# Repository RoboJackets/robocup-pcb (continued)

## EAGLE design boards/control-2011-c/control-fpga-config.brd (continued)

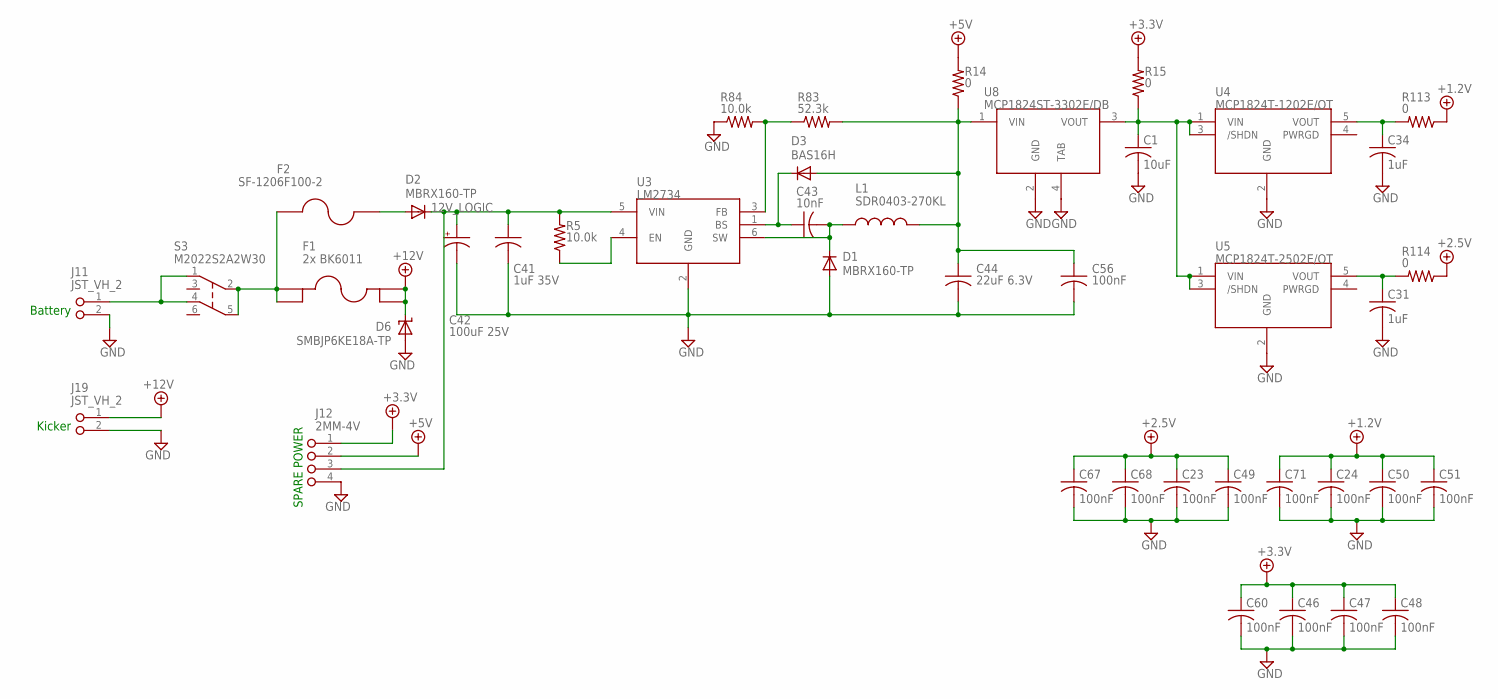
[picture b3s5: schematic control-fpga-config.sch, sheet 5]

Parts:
C1: 10uF; C0805
C23, C24, C46, C47, C48, C49, C50, C51, C56, C60, C67, C68, C71: 100nF; C0603
C31, C34: 1uF; C0603
C41: 1uF 35V; C0805
C42: 100uF 25V; PANASONIC_E
C43: 10nF; C0603
C44: 22uF 6.3V; C1206
D1, D2: MBRX160-TP; SOD123
D3: BAS16H; SOD323-W
D6: SMBJP6KE18A-TP; SMBJ
F1: 2x BK6011; FUSE_MINI_ATC
F2: SF-1206F100-2; F1206
J11, J19: JST_VH_2; JST_VH_2_RA
J12: 2MM-4V; 2MM-4-V
L1: SDR0403-270KL; SDR0403
R5, R84: 10.0k; R0603
R14, R15, R113, R114: 0; R0603
R83: 52.3k; R0603
S3: M2022S2A2W30; M202X-30
U3: LM2734; SOT23-6L
U4: MCP1824T-1202E/OT; SOT23-5
U5: MCP1824T-2502E/OT; SOT23-5
U8: MCP1824ST-3302E/DB; SOT223

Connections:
12V_LOGIC: C41.1, C42.+, D2.C, J12.3, R5.2, U3.5 (VIN)
+1.2V: C24.1, C50.1, C51.1, C71.1, R113.1; also elsewhere on the board
+2.5V: C23.1, C49.1, C67.1, C68.1, R114.1; also elsewhere on the board
+3.3V: C46.1, C47.1, C48.1, C60.1, J12.1, R15.2; also elsewhere on the board
+5V: J12.2, R14.2; also elsewhere on the board
+12V: D6.C, F1.3, F1.4, J19.1; also elsewhere on the board
GND: C1.2, C23.2, C24.2, C31.2, C34.2, C41.2, C42.-, C44.2, C46.2, C47.2, C48.2, C49.2, C50.2, C51.2, C56.2, C60.2, C67.2, C68.2, C71.2, D1.A, D6.A, J11.2, J12.4, J19.2, R84.1, U3.2 (GND), U4.2 (GND), U5.2 (GND), U8.2 (GND), U8.4 (TAB); also elsewhere on the board
unnamed: C44.1, C56.1, D3.A, L1.2, R14.1, R83.2, U8.1 (VIN)
unnamed: C1.1, R15.1, U4.1 (VIN), U4.3 (/SHDN), U5.1 (VIN), U5.3 (/SHDN), U8.3 (VOUT)
unnamed: C43.2, D1.C, L1.1, U3.6 (SW)
unnamed: C34.1, R113.2, U4.5 (VOUT)
unnamed: C31.1, R114.2, U5.5 (VOUT)
unnamed: J11.1, S3.1 (NC1), S3.4 (NC2)
unnamed: R5.1, U3.4 (EN)
unnamed: C43.1, D3.C, U3.1 (BS)
unnamed: F1.1, F1.2, F2.1, S3.2 (C1), S3.5 (C2)
unnamed: R83.1, R84.2, U3.3 (FB)
unnamed: D2.A, F2.2

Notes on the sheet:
Kicker
Battery
SPARE POWER

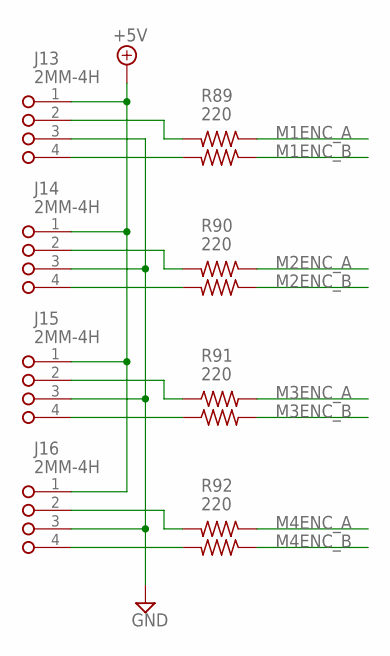
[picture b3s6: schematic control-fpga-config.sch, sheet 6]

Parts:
J13, J14, J15, J16: 2MM-4H; 2MM-4-H
R89, R90, R91, R92: 220; RA_2_0606

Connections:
+5V: J13.1, J14.1, J15.1, J16.1; also elsewhere on the board
GND: J13.3, J14.3, J15.3, J16.3; also elsewhere on the board
M1ENC_A: R89.1; also elsewhere on the board
M1ENC_B: R89.3; also elsewhere on the board
M2ENC_A: R90.1; also elsewhere on the board
M2ENC_B: R90.3; also elsewhere on the board
M3ENC_A: R91.2; also elsewhere on the board
M3ENC_B: R91.4; also elsewhere on the board
M4ENC_A: R92.1; also elsewhere on the board
M4ENC_B: R92.3; also elsewhere on the board
unnamed: J13.4, R89.4
unnamed: J13.2, R89.2
unnamed: J16.4, R92.4
unnamed: J16.2, R92.2
unnamed: J15.4, R91.3
unnamed: J15.2, R91.1
unnamed: J14.4, R90.4
unnamed: J14.2, R90.2

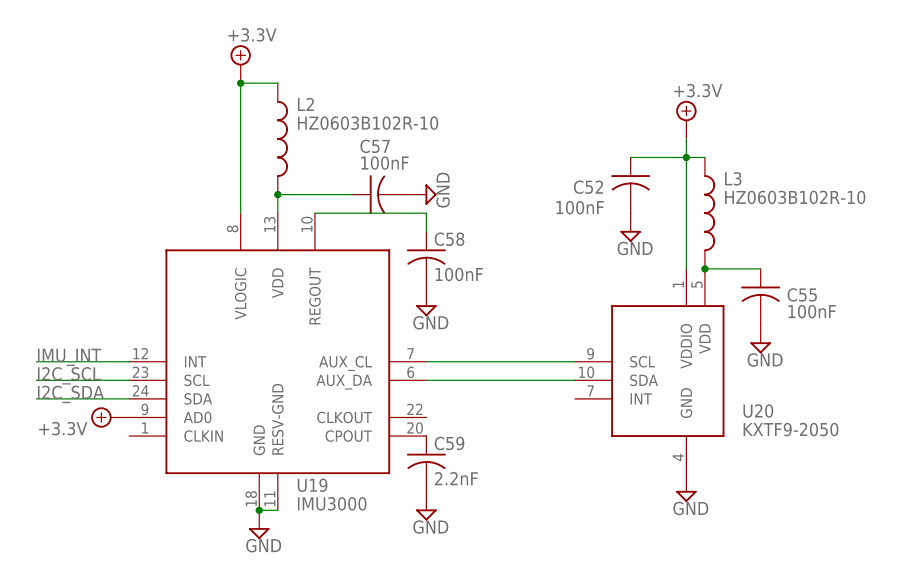
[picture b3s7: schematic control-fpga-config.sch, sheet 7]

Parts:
C52, C55, C57, C58: 100nF; C0603
C59: 2.2nF; C0603
L2, L3: HZ0603B102R-10; C0603
U19: IMU3000
U20: KXTF9-2050; KXTF9

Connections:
+3.3V: C52.1, L2.1, L3.1, U19.8 (VLOGIC), U19.9 (AD0), U20.1 (VDDIO); also elsewhere on the board
GND: C52.2, C55.2, C57.2, C58.2, C59.2, U19.11 (RESV-GND), U19.18 (GND), U20.4 (GND); also elsewhere on the board
I2C_SCL: U19.23 (SCL); also elsewhere on the board
I2C_SDA: U19.24 (SDA); also elsewhere on the board
IMU_INT: U19.12 (INT); also elsewhere on the board
unnamed: C55.1, L3.2, U20.5 (VDD)
unnamed: U19.7 (AUX_CL), U20.9 (SCL)
unnamed: U19.6 (AUX_DA), U20.10 (SDA)
unnamed: C57.1, L2.2, U19.13 (VDD)
unnamed: C58.1, U19.10 (REGOUT)
unnamed: C59.1, U19.20 (CPOUT)

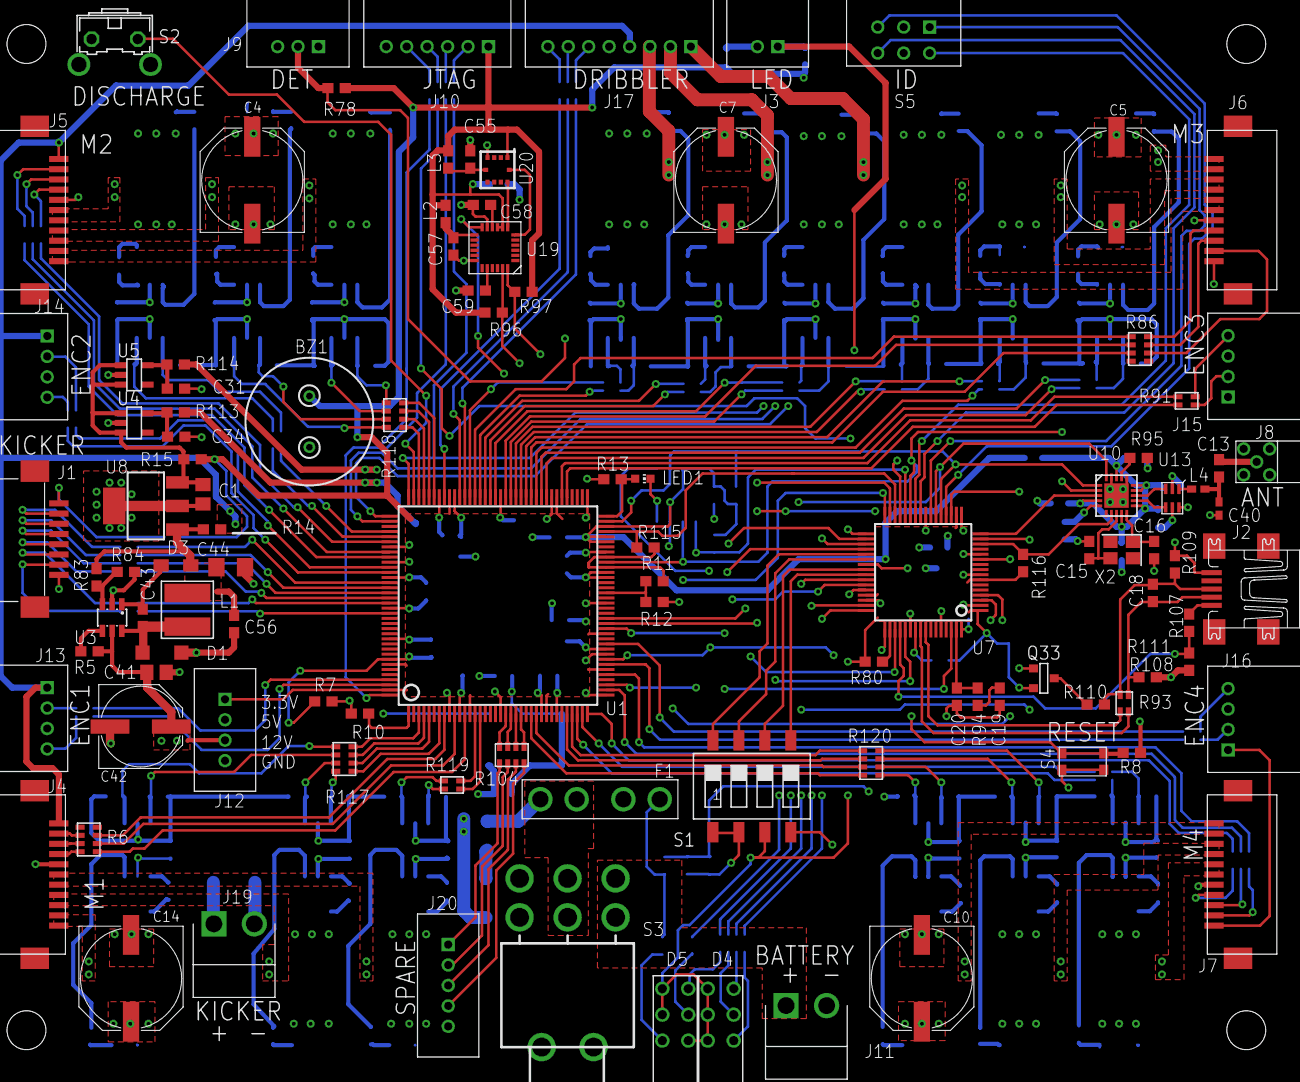
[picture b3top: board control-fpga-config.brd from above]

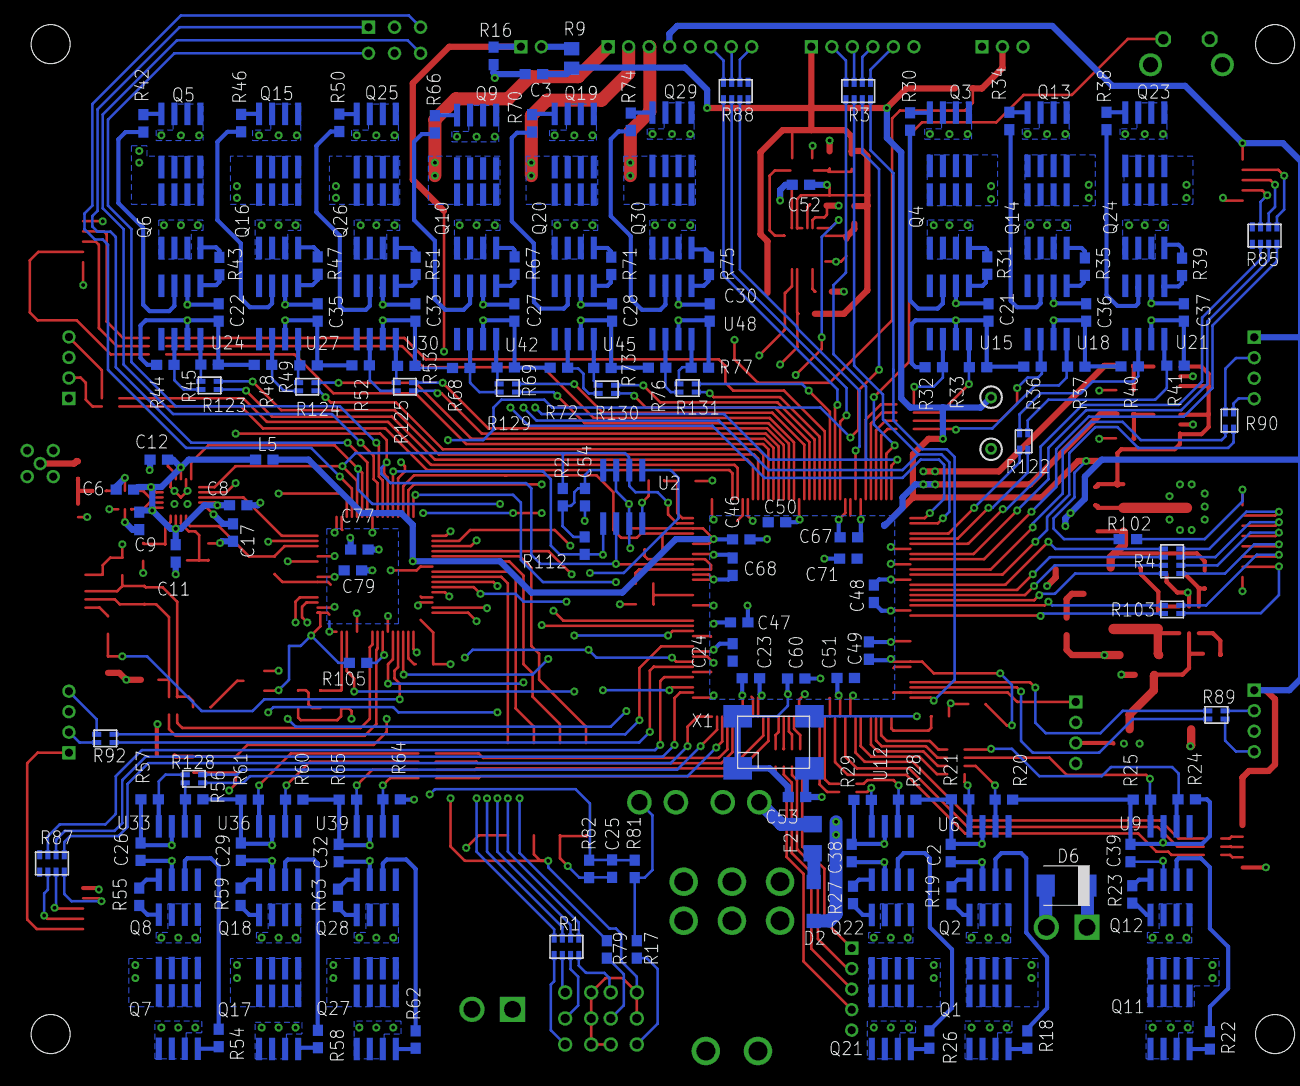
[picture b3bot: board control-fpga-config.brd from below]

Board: 4 copper layers, 285 parts (179 on the bottom side), 301 nets.

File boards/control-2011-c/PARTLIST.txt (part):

Partlist

Exported from control-2011-c.brd at 10/16/2014 2:49:54 AM

EAGLE Version 6.5.0 Copyright (c) 1988-2013 CadSoft

Assembly variant: 

Part     Value              Package         Library          Position (inch)       Orientation

BZ1      PS12               PS12            tdk              (1.09 2.345)          R90
C1       10uF               C0805           rcl              (0.68 2.065)          R270
C2       100nF              C0603           rcl              (1.245 0.695)         MR90
C3       1uF                C0603           rcl              (2.845 3.685)         MR180
C4       470uF 25V          PANASONIC_G     rcl              (0.87 3.275)          R90
C5       470uF 25V          PANASONIC_G     rcl              (4.2 3.275)           R90
C6       100nF              C0603           rcl              (4.415 2.09)          MR180
C7       470uF 25V          PANASONIC_G     rcl              (2.695 3.275)         R90
C8       10nF               C0603           rcl              (3.98 2.03)           MR0
C9       2.2nF              C0603           rcl              (4.36 1.97)           MR270
C10      470uF 25V          PANASONIC_G     rcl              (3.45 0.2)            R270
C11      10nF               C0603           rcl              (4.22 1.845)          MR270
C12      220nF              C0603           rcl              (4.285 2.205)         MR180
C13      100pF              C0603           rcl              (4.595 2.165)         R90
C14      470uF 25V          PANASONIC_G     rcl              (0.403 0.2)           R270
C15      27pF               C0603           rcl              (4.095 1.85)          R90
C16      27pF               C0603           rcl              (4.345 1.85)          R270
C17      100nF              C0603           rcl              (4 1.925)             MR270
C18      33pF               C0603           rcl              (4.34 1.685)          R270
C19      10nF               C0603           rcl              (3.75 1.285)          R270
C20      1nF                C0603           rcl              (3.585 1.285)         R270
C21      100nF              C0603           rcl              (1.1 2.77)            MR270
C22      100nF              C0603           rcl              (4.055 2.77)          MR270
C23      100nF              C0603           rcl              (2.012 1.366)         MR0
C24      100nF              C0603           rcl              (2.082 1.465)         MR90
C25      100nF              C0603           rcl              (2.545 0.635)         MR270
C26      100nF              C0603           rcl              (4.355 0.7)           MR90
C27      100nF              C0603           rcl              (2.92 2.77)           MR270
C28      100nF              C0603           rcl              (2.545 2.77)          MR270
C29      100nF              C0603           rcl              (3.97 0.7)            MR90
C30      100nF              C0603           rcl              (2.17 2.77)           MR270
C31      1uF                C0603           rcl              (0.576 2.472)         R0
C32      100nF              C0603           rcl              (3.595 0.695)         MR90
C33      100nF              C0603           rcl              (3.3 2.77)            MR270
C34      1uF                C0603           rcl              (0.577 2.287)         R0
C35      100nF              C0603           rcl              (3.675 2.77)          MR270
C36      100nF              C0603           rcl              (0.725 2.77)          MR270
C37      100nF              C0603           rcl              (0.35 2.77)           MR270
C38      100nF              C0603           rcl              (1.625 0.695)         MR90
C39      100nF              C0603           rcl              (0.555 0.695)         MR90
C40      500R07S1R8BV4T     C0402           rcl              (4.595 2.01)          R270
C41      1uF 35V            C0805           rcl              (0.501 1.379)         R0
C42      100uF 25V          PANASONIC_E     rcl              (0.44 1.17)           R0
C43      10nF               C0603           rcl              (0.448 1.589)         R270
C44      22uF 6.3V          C1206           rcl              (0.787 1.784)         R0
C46      100nF              C0603           rcl              (2.049 1.899)         MR0
C47      100nF              C0603           rcl              (2.057 1.58)          MR0
C48      100nF              C0603           rcl              (1.54 1.69)           MR270
C49      100nF              C0603           rcl              (1.559 1.472)         MR90
C50      100nF              C0603           rcl              (1.912 1.965)         MR0
C51      100nF              C0603           rcl              (1.648 1.367)         MR180
C52      100nF              C0603           rcl              (1.82 3.26)           MR180
C53      100nF              C0603           rcl              (1.835 0.91)          MR0
C54      100nF              C0603           rcl              (2.649 2.061)         MR270
C55      100nF              C0603           rcl              (1.71 3.355)          R90
C56      100nF              C0603           rcl              (0.8 1.565)           R270
C57      100nF              C0603           rcl              (1.645 3.02)          R270
C58      100nF              C0603           rcl              (1.755 3.18)          R180
C59      2.2nF              C0603           rcl              (1.735 2.85)          R180
C60      100nF              C0603           rcl              (1.838 1.365)         MR0
C67      100nF              C0603           rcl              (1.636 1.907)         MR180
C68      100nF              C0603           rcl              (2.082 1.794)         MR270
C71      100nF              C0603           rcl              (1.638 1.825)         MR180
C77      100nF              C0603           rcl              (3.515 1.86)          MR0
C79      100nF              C0603           rcl              (3.54 1.78)           MR0
D1       MBRX160-TP         SOD123          diode            (0.522 1.455)         R0
D2       MBRX160-TP         SOD123          diode            (1.771 0.509)         MR90
D3       BAS16H             SOD323-W        diode            (0.576 1.791)         R0
D4       564-0100-132F      DIALIGHT-564    led-array        (2.625 -0.04)         R0
D5       564-0100-132F      DIALIGHT-564    led-array        (2.45 -0.04)          R0
D6       SMBJP6KE18A-TP     SMBJ            power            (0.8 0.57)            MR180
F1       2x BK6011          FUSE_MINI_ATC   power            (2.21 0.89)           R0
F2       SF-1206F100-2      F1206           power            (1.775 0.75)          MR270
J1       0528520870         0528520870      con-robocup      (0.125 2.03)          R270
J2       MINI-USB           UX60A-MB-5ST    con-robocup      (4.655 1.7)           R180
J3       2MM-2H             2MM-2-H         2mm              (2.895 3.79)          R0
J4       Molex 0522711179   FH_11_HOR       hirose           (0.15 0.6)            R90
J5       Molex 0522711179   FH_11_HOR       hirose           (0.15 3.16)           R90
J6       Molex 0522711179   FH_11_HOR       hirose           (4.55 3.16)           R270
J7       Molex 0522711179   FH_11_HOR       hirose           (4.55 0.6)            R270
J8       MMCX_RA            MMCX_RA         radio            (4.74 2.19)           R0
J9       2MM-3H             2MM-3-H         2mm              (1.125 3.79)          R0
J10      2MM-6H             2MM-6-H         2mm              (1.78 3.79)           R0
J11      JST_VH_2           JST_VH_2_RA     jst_vh           (3.005 0.095)         R0
J12      2MM-4V             2MM-4-V         2mm              (0.765 1.275)         R90
J13      2MM-4H             2MM-4-H         2mm              (0.08 1.32)           R90
J14      2MM-4H             2MM-4-H         2mm              (0.08 2.675)          R90
J15      2MM-4H             2MM-4-H         2mm              (4.63 2.44)           R270
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
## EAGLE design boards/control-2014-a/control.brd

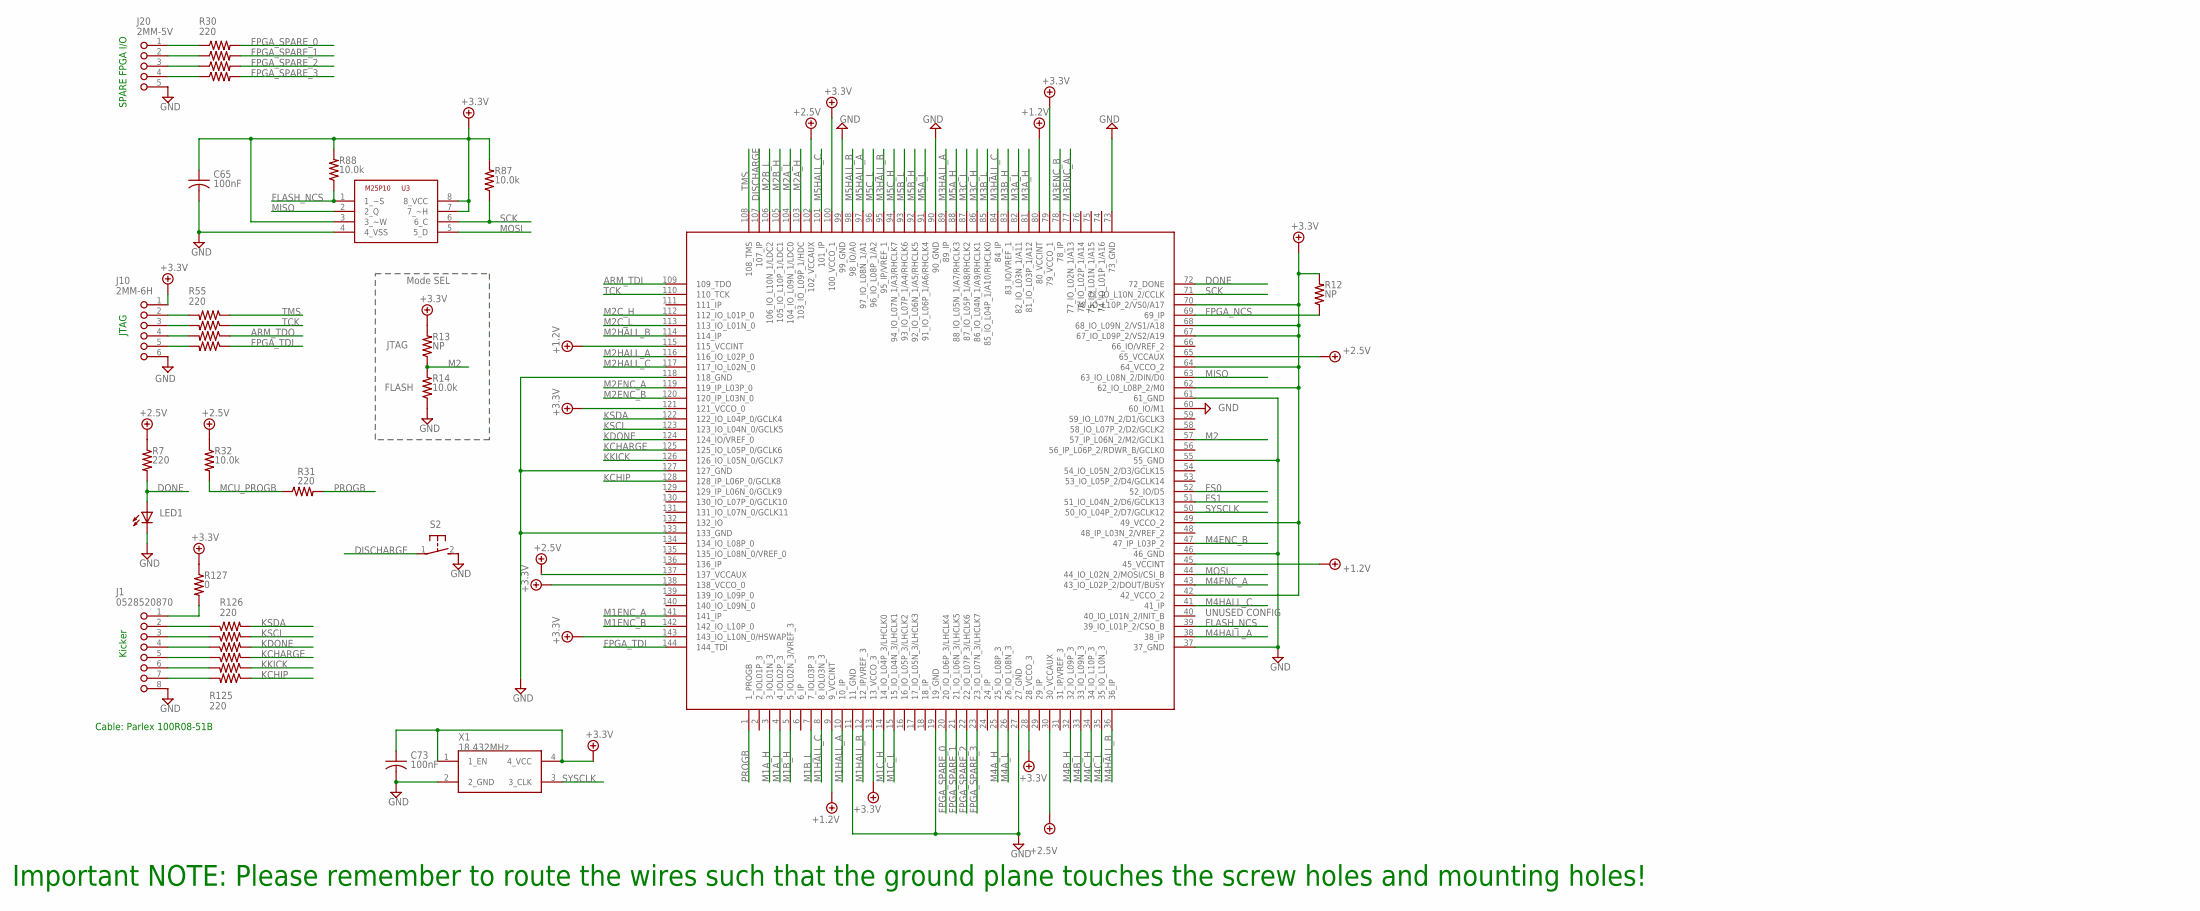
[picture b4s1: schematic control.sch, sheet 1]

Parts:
C65, C73: 100nF; C0603
J1: 0528520870
J10: 2MM-6H; 2MM-6-H
J20: 2MM-5V; 2MM-5-V
LED1: LEDCHIP-LED0603; CHIP-LED0603
R7, R31: 220; R0603
R12, R13: NP; R0603
R14, R32, R87, R88: 10.0k; R0603
R30, R55, R126: 220; RA_4_1206
R125: 220; RA_2_0606
R127: 0; R0603
S2: 31-XX; B3F-31XX
U1: XC3S100E; TQFP144
U3: M25P10; SO08
X1: 18.432MHz; XTAL_LCC

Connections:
+1.2V: U1.9 (9_VCCINT), U1.45 (45_VCCINT), U1.80 (80_VCCINT), U1.115 (115_VCCINT); also elsewhere on the board
+2.5V: R7.1, R32.1, U1.30 (30_VCCAUX), U1.65 (65_VCCAUX), U1.102 (102_VCCAUX), U1.137 (137_VCCAUX); also elsewhere on the board
+3.3V: C65.1, C73.1, J10.1, R12.2, R13.2, R87.2, R88.2, R127.1, U1.13 (13_VCCO_3), U1.28 (28_VCCO_3), U1.42 (42_VCCO_2), U1.49 (49_VCCO_2), U1.62 (62_IO_L08P_2/M0), U1.64 (64_VCCO_2), U1.67 (67_IO_L09P_2/VS2/A19), U1.68 (68_IO_L09N_2/VS1/A18), U1.70 (70_IO_L10P_2/VS0/A17), U1.79 (79_VCCO_1), U1.100 (100_VCCO_1), U1.121 (121_VCCO_0), U1.138 (138_VCCO_0), U1.143 (143_IO_L10N_0/HSWAP), U3.3 (3_~W), U3.7 (7_~H), U3.8 (8_VCC), X1.1 (1_EN), X1.4 (4_VCC); also elsewhere on the board
ARM_TDI: U1.109 (109_TDO); also elsewhere on the board
ARM_TDO: R55.5; also elsewhere on the board
DISCHARGE: S2.1, U1.107 (107_IP)
DONE: LED1.A, R7.2, U1.72 (72_DONE)
FLASH_NCS: R88.1, U1.39 (39_IO_L01P_2/CSO_B), U3.1 (1_~S); also elsewhere on the board
FPGA_NCS: R12.1, U1.69 (69_IP); also elsewhere on the board
FPGA_SPARE_0: R30.2, U1.20 (20_IO_L06P_3/LHCLK4)
FPGA_SPARE_1: R30.4, U1.21 (21_IO_L06N_3/LHCLK5)
FPGA_SPARE_2: R30.6, U1.22 (22_IO_L07P_3/LHCLK6)
FPGA_SPARE_3: R30.8, U1.23 (23_IO_L07N_3/LHCLK7)
FPGA_TDI: R55.7, U1.144 (144_TDI)
FS0: U1.52 (52_IO/D5); also elsewhere on the board
FS1: U1.51 (51_IO_L04N_2/D6/GCLK13); also elsewhere on the board
GND: C65.2, C73.2, J1.8, J10.6, J20.5, LED1.C, R14.1, S2.2 (S), U1.11 (11_GND), U1.19 (19_GND), U1.27 (27_GND), U1.37 (37_GND), U1.46 (46_GND), U1.55 (55_GND), U1.60 (60_IO/M1), U1.61 (61_GND), U1.73 (73_GND), U1.90 (90_GND), U1.99 (99_GND), U1.118 (118_GND), U1.127 (127_GND), U1.133 (133_GND), U3.4 (4_VSS), X1.2 (2_GND); also elsewhere on the board
KCHARGE: R126.2, U1.125 (125_IO_L05P_0/GCLK6)
KCHIP: R125.3, U1.128 (128_IP_L06P_0/GCLK8)
KDONE: R126.4, U1.124 (124_IO/VREF_0)
KKICK: R125.1, U1.126 (126_IO_L05N_0/GCLK7)
KSCL: R126.6, U1.123 (123_IO_L04N_0/GCLK5)
KSDA: R126.8, U1.122 (122_IO_L04P_0/GCLK4)
M1A_H: U1.3 (3_IOL01N_3); also elsewhere on the board
M1A_L: U1.4 (4_IOL02P_3); also elsewhere on the board
M1B_H: U1.5 (5_IOL02N_3/VREF_3); also elsewhere on the board
M1B_L: U1.7 (7_IOL03P_3); also elsewhere on the board
M1C_H: U1.14 (14_IO_L04P_3/LHCLK0); also elsewhere on the board
M1C_L: U1.15 (15_IO_L04N_3/LHCLK1); also elsewhere on the board
M1ENC_A: U1.141 (141_IP); also elsewhere on the board
M1ENC_B: U1.142 (142_IO_L10P_0); also elsewhere on the board
M1HALL_A: U1.10 (10_IP); also elsewhere on the board
M1HALL_B: U1.12 (12_IP/VREF_3); also elsewhere on the board
M1HALL_C: U1.8 (8_IOL03N_3); also elsewhere on the board
M2: R13.1, R14.2, U1.57 (57_IP_L06N_2/M2/GCLK1)
M2A_H: U1.103 (103_IO_L09P_1/HDC); also elsewhere on the board
M2A_L: U1.104 (104_IO_L09N_1/LDC0); also elsewhere on the board
M2B_H: U1.105 (105_IO_L10P_1/LDC1); also elsewhere on the board
M2B_L: U1.106 (106_IO_L10N_1/LDC2); also elsewhere on the board
M2C_H: U1.112 (112_IO_L01P_0); also elsewhere on the board
M2C_L: U1.113 (113_IO_L01N_0); also elsewhere on the board
M2ENC_A: U1.119 (119_IP_L03P_0); also elsewhere on the board
M2ENC_B: U1.120 (120_IP_L03N_0); also elsewhere on the board
M2HALL_A: U1.116 (116_IO_L02P_0); also elsewhere on the board
M2HALL_B: U1.114 (114_IP); also elsewhere on the board
M2HALL_C: U1.117 (117_IO_L02N_0); also elsewhere on the board
M3A_H: U1.81 (81_IO_L03P_1/A12); also elsewhere on the board
M3A_L: U1.82 (82_IO_L03N_1/A11); also elsewhere on the board
M3B_H: U1.83 (83_IO/VREF_1); also elsewhere on the board
M3B_L: U1.85 (85_IO_L04P_1/A10/RHCLK0); also elsewhere on the board
M3C_H: U1.86 (86_IO_L04N_1/A9/RHCLK1); also elsewhere on the board
M3C_L: U1.87 (87_IO_L05P_1/A8/RHCLK2); also elsewhere on the board
M3ENC_A: U1.77 (77_IO_L02N_1/A13); also elsewhere on the board
M3ENC_B: U1.78 (78_IP); also elsewhere on the board
M3HALL_A: U1.89 (89_IP); also elsewhere on the board
M3HALL_B: U1.95 (95_IP/VREF_1); also elsewhere on the board
M3HALL_C: U1.84 (84_IP); also elsewhere on the board
M4A_H: U1.25 (25_IO_L08P_3); also elsewhere on the board
M4A_L: U1.26 (26_IO_L08N_3); also elsewhere on the board
M4B_H: U1.32 (32_IO_L09P_3); also elsewhere on the board
M4B_L: U1.33 (33_IO_L09N_3); also elsewhere on the board
M4C_H: U1.34 (34_IO_L10P_3); also elsewhere on the board
M4C_L: U1.35 (35_IO_L10N_3); also elsewhere on the board
M4ENC_A: U1.43 (43_IO_L02P_2/DOUT/BUSY); also elsewhere on the board
M4ENC_B: U1.47 (47_IP_L03P_2); also elsewhere on the board
M4HALL_A: U1.38 (38_IP); also elsewhere on the board
M4HALL_B: U1.36 (36_IP); also elsewhere on the board
M4HALL_C: U1.41 (41_IP); also elsewhere on the board
M5A_H: U1.88 (88_IO_L05N_1/A7/RHCLK3); also elsewhere on the board
M5A_L: U1.91 (91_IO_L06P_1/A6/RHCLK4); also elsewhere on the board
M5B_H: U1.92 (92_IO_L06N_1/A5/RHCLK5); also elsewhere on the board
M5B_L: U1.93 (93_IO_L07P_1/A4/RHCLK6); also elsewhere on the board
M5C_H: U1.94 (94_IO_L07N_1/A3/RHCLK7); also elsewhere on the board
M5C_L: U1.96 (96_IO_L08P_1/A2); also elsewhere on the board
M5HALL_A: U1.97 (97_IO_L08N_1/A1); also elsewhere on the board
M5HALL_B: U1.98 (98_IO/A0); also elsewhere on the board
M5HALL_C: U1.101 (101_IP); also elsewhere on the board
MCU_PROGB: R31.1, R32.2; also elsewhere on the board
MISO: U1.63 (63_IO_L08N_2/DIN/D0), U3.2 (2_Q); also elsewhere on the board
MOSI: U1.44 (44_IO_L02N_2/MOSI/CSI_B), U3.5 (5_D); also elsewhere on the board
unnamed: J10.3, R55.4
unnamed: J10.5, R55.8
unnamed: J1.2, R126.7
unnamed: J1.3, R126.5
unnamed: J1.4, R126.3
unnamed: J1.5, R126.1
unnamed: J10.4, R55.6
unnamed: J10.2, R55.2
unnamed: J1.6, R125.2
unnamed: J1.7, R125.4
unnamed: J1.1, R127.2
unnamed: J20.3, R30.5
unnamed: J20.2, R30.3
unnamed: J20.1, R30.1
unnamed: J20.4, R30.7
PROGB: R31.2, U1.1 (1_PROGB)
SCK: R87.1, U1.71 (71_IO_L10N_2/CCLK), U3.6 (6_C); also elsewhere on the board
SYSCLK: U1.50 (50_IO_L04P_2/D7/GCLK12), X1.3 (3_CLK); also elsewhere on the board
TCK: R55.3, U1.110 (110_TCK); also elsewhere on the board
TMS: R55.1, U1.108 (108_TMS); also elsewhere on the board

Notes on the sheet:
JTAG
FLASH
Mode SEL
Kicker
UNUSED CONFIG
SPARE FPGA I/O
Cable: Parlex 100R08-51B
Important NOTE: Please remember to route the wires such that the ground plane touches the screw holes and mounting holes!

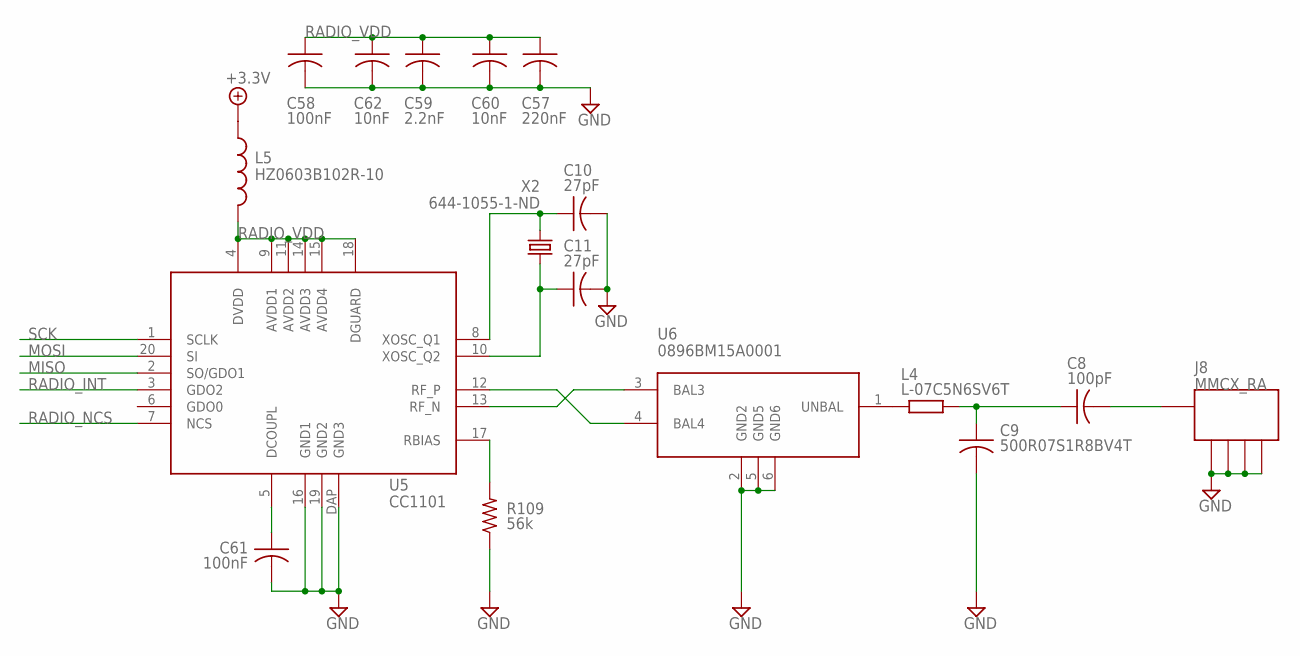
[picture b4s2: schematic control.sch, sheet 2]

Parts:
C8: 100pF; C0603
C9: 500R07S1R8BV4T; C0402
C10, C11: 27pF; C0603
C57: 220nF; C0603
C58, C61: 100nF; C0603
C59: 2.2nF; C0603
C60, C62: 10nF; C0603
J8: MMCX_RA
L4: L-07C5N6SV6T; R0402
L5: HZ0603B102R-10; C0603
R109: 56k; R0603
U5: CC1101; QLP20
U6: 0896BM15A0001
X2: 644-1055-1-ND; XTAL-3.2X2.5

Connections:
+3.3V: L5.1; also elsewhere on the board
GND: C9.2, C10.2, C11.2, C57.2, C58.2, C59.2, C60.2, C61.2, C62.2, J8.P$2, J8.P$3, J8.P$4, J8.P$5, R109.1, U5.16 (GND1), U5.19 (GND2), U5.DAP (GND3), U6.2 (GND2), U6.5 (GND5), U6.6 (GND6); also elsewhere on the board
MISO: U5.2 (SO/GDO1); also elsewhere on the board
MOSI: U5.20 (SI); also elsewhere on the board
unnamed: C61.1, U5.5 (DCOUPL)
unnamed: R109.2, U5.17 (RBIAS)
unnamed: C11.1, U5.10 (XOSC_Q2), X2.1
unnamed: C10.1, U5.8 (XOSC_Q1), X2.3 (2)
unnamed: L4.1, U6.1 (UNBAL)
unnamed: C8.1, C9.1, L4.2
unnamed: U5.12 (RF_P), U6.4 (BAL4)
unnamed: U5.13 (RF_N), U6.3 (BAL3)
unnamed: C8.2, J8.P$1
RADIO_INT: U5.3 (GDO2); also elsewhere on the board
RADIO_NCS: U5.7 (NCS); also elsewhere on the board
RADIO_VDD: C57.1, C58.1, C59.1, C60.1, C62.1, L5.2, U5.4 (DVDD), U5.9 (AVDD1), U5.11 (AVDD2), U5.14 (AVDD3), U5.15 (AVDD4), U5.18 (DGUARD)
SCK: U5.1 (SCLK); also elsewhere on the board

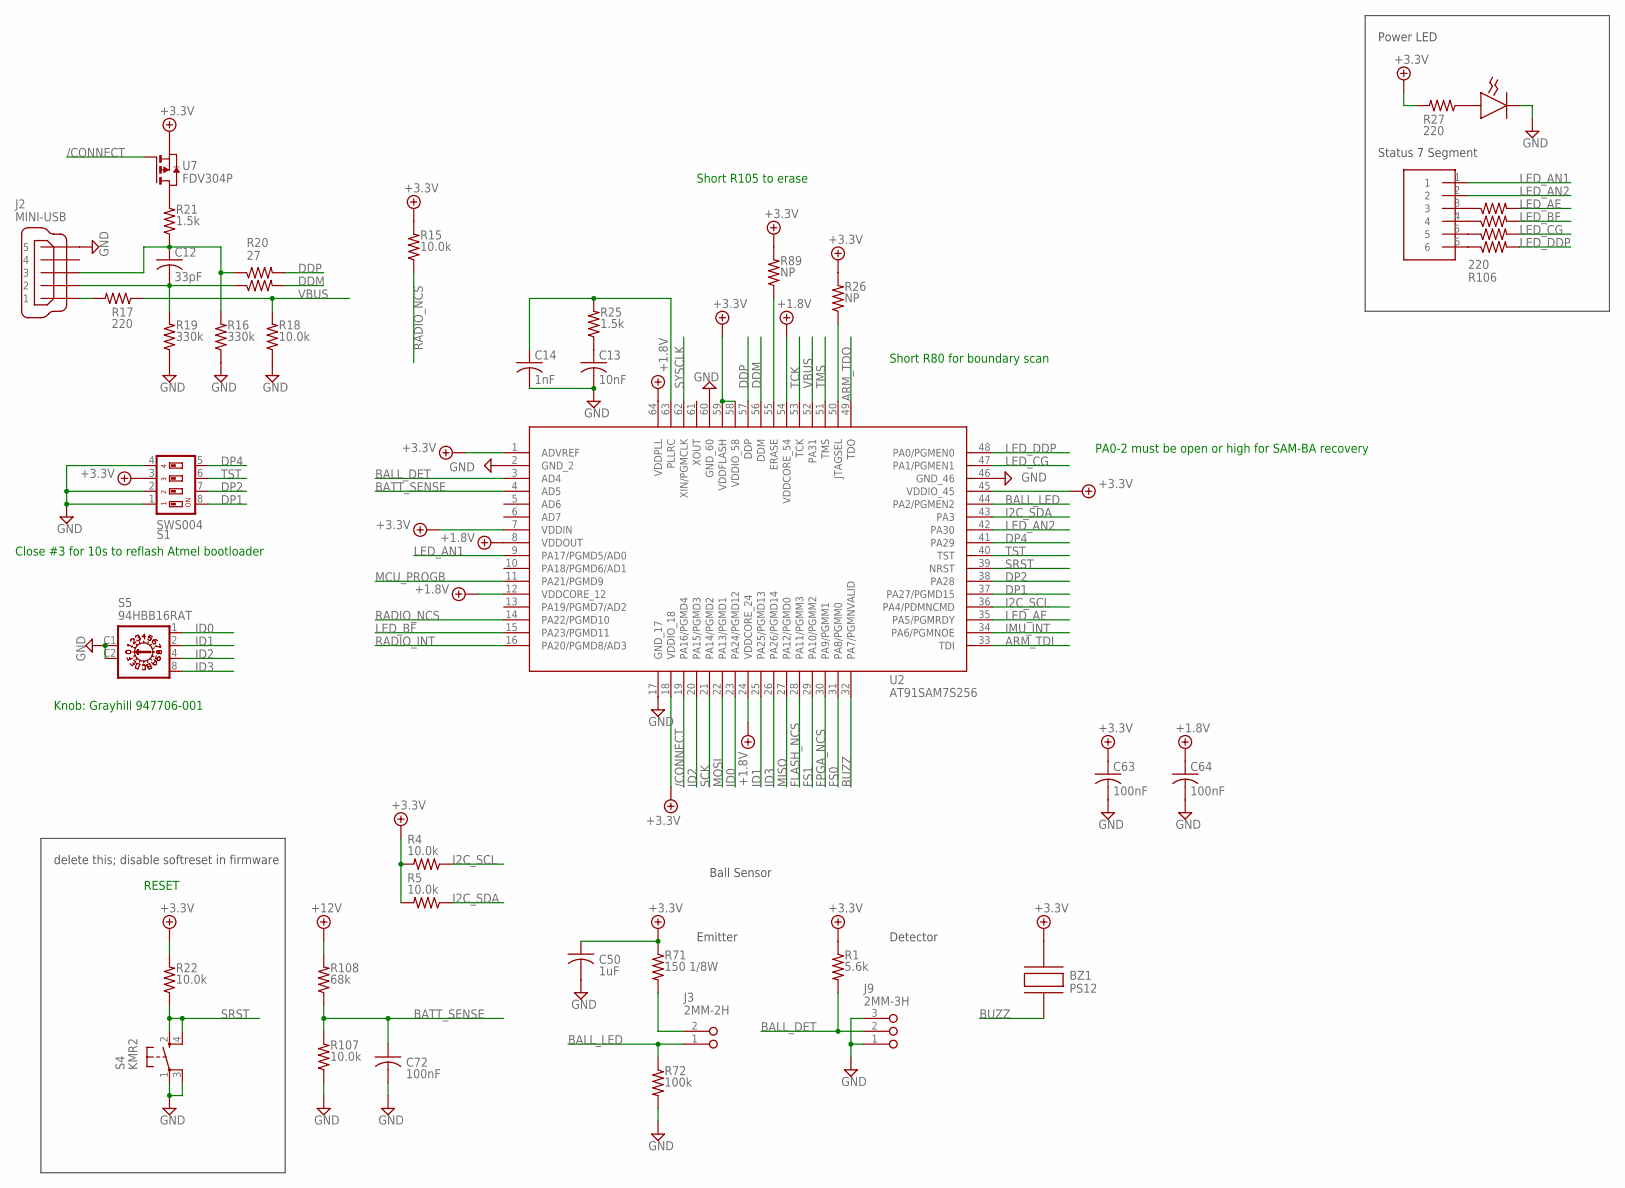
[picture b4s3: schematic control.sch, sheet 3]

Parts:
BZ1: PS12
C12: 33pF; C0603
C13: 10nF; C0603
C14: 1nF; C0603
C50: 1uF; C0603
C63, C64, C72: 100nF; C0603
J2: MINI-USB; UX60A-MB-5ST
J3: 2MM-2H; 2MM-2-H
J9: 2MM-3H; 2MM-3-H
LED2: LED2; 5350T5
LED3: LDS-M514RI-RA
R1: 5.6k; R0603
R4, R5, R15, R18, R22, R107: 10.0k; R0603
R16, R19: 330k; R0603
R17, R27: 220; R0603
R20: 27; RA_2_0606
R21, R25: 1.5k; R0603
R26, R89: NP; R0603
R71: 150 1/8W; R0805
R72: 100k; R0603
R106: 220; RA_4_1206
R108: 68k; R0603
S1: SWS004; SMS-004
S4: KMR2
S5: 94HBB16RAT; HEX-RA-2C
U2: AT91SAM7S256; SQFP-S-10X10-64
U7: FDV304P; SOT-23

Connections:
+1.8V: C64.1, U2.8 (VDDOUT), U2.12 (VDDCORE_12), U2.24 (VDDCORE_24), U2.54 (VDDCORE_54), U2.64 (VDDPLL); also elsewhere on the board
+3.3V: BZ1.2, C50.1, C63.1, R1.1, R4.2, R5.2, R15.2, R22.2, R26.2, R27.2, R71.1, R89.2, S1.3, U2.1 (ADVREF), U2.7 (VDDIN), U2.18 (VDDIO_18), U2.45 (VDDIO_45), U2.58 (VDDIO_58), U2.59 (VDDFLASH), U7.2 (S); also elsewhere on the board
+12V: R108.2; also elsewhere on the board
/CONNECT: U2.19 (PA16/PGMD4), U7.3 (G)
ARM_TDI: U2.33 (TDI); also elsewhere on the board
ARM_TDO: U2.49 (TDO); also elsewhere on the board
BALL_DET: J9.2, R1.2, U2.3 (AD4)
BALL_LED: J3.1, R72.1, U2.44 (PA2/PGMEN2)
BATT_SENSE: C72.1, R107.2, R108.1, U2.4 (AD5)
BUZZ: BZ1.1, U2.32 (PA7/PGMNVALID)
DDM: R20.2, U2.56 (DDM)
DDP: R20.4, U2.57 (DDP)
DP1: S1.8, U2.37 (PA27/PGMD15)
DP2: S1.7, U2.38 (PA28)
DP4: S1.5, U2.41 (PA29)
FLASH_NCS: U2.28 (PA11/PGMM3); also elsewhere on the board
FPGA_NCS: U2.30 (PA9/PGMM1); also elsewhere on the board
FS0: U2.31 (PA8/PGMM0); also elsewhere on the board
FS1: U2.29 (PA10/PGMM2); also elsewhere on the board
GND: C13.2, C14.2, C50.2, C63.2, C64.2, C72.2, J2.5, J9.1, J9.3, LED2.CATHODE (2), R16.1, R18.1, R19.1, R72.2, R107.1, S1.1, S1.2, S1.4, S4.1, S4.3, S5.C1, S5.C2, U2.2 (GND_2), U2.17 (GND_17), U2.46 (GND_46), U2.60 (GND_60); also elsewhere on the board
I2C_SCL: R4.1, U2.36 (PA4/PDMNCMD); also elsewhere on the board
I2C_SDA: R5.1, U2.43 (PA3); also elsewhere on the board
ID0: S5.1, U2.23 (PA24/PGMD12)
ID1: S5.2, U2.25 (PA25/PGMD13)
ID2: S5.4, U2.20 (PA15/PGMD3)
ID3: S5.8, U2.26 (PA26/PGMD14)
IMU_INT: U2.34 (PA6/PGMNOE); also elsewhere on the board
LED_AE: R106.8, U2.35 (PA5/PGMRDY)
LED_AN1: LED3.1, U2.9 (PA17/PGMD5/AD0)
LED_AN2: LED3.2, U2.42 (PA30)
LED_BF: R106.6, U2.15 (PA23/PGMD11)
LED_CG: R106.4, U2.47 (PA1/PGMEN1)
LED_DDP: R106.2, U2.48 (PA0/PGMEN0)
MCU_PROGB: U2.11 (PA21/PGMD9); also elsewhere on the board
MISO: U2.27 (PA12/PGMD0); also elsewhere on the board
MOSI: U2.22 (PA13/PGMD1); also elsewhere on the board
unnamed: LED3.6, R106.1
unnamed: LED3.5, R106.3
unnamed: LED3.4, R106.5
unnamed: LED3.3, R106.7
unnamed: LED2.ANODE (1), R27.1
unnamed: J3.2, R71.2
unnamed: R26.1, U2.50 (JTAGSEL)
unnamed: C12.2, J2.2, R19.2, R20.1
unnamed: R89.1, U2.55 (ERASE)
unnamed: C12.1, J2.3, R16.2, R20.3, R21.1
unnamed: R21.2, U7.1 (D)
unnamed: C13.1, R25.1
unnamed: C14.1, R25.2, U2.63 (PLLRC)
unnamed: J2.1, R17.2
RADIO_INT: U2.16 (PA20/PGMD8/AD3); also elsewhere on the board
RADIO_NCS: R15.1, U2.14 (PA22/PGMD10); also elsewhere on the board
SCK: U2.21 (PA14/PGMD2); also elsewhere on the board
SRST: R22.1, S4.2, S4.4, U2.39 (NRST)
SYSCLK: U2.62 (XIN/PGMCLK); also elsewhere on the board
TCK: U2.53 (TCK); also elsewhere on the board
TMS: U2.51 (TMS); also elsewhere on the board
TST: S1.6, U2.40 (TST)
VBUS: R17.1, R18.2, U2.52 (PA31)

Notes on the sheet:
RESET
Ball Sensor
Emitter
Detector
PA0-2 must be open or high for SAM-BA recovery
Close #3 for 10s to reflash Atmel bootloader
Short R105 to erase
Short R80 for boundary scan
Knob: Grayhill 947706-001
delete this; disable softreset in firmware
Status 7 Segment
Power LED
